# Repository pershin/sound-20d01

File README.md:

# Sound-20D01

## Sound-20D01MB

### Bill of Materials

| Reference                                                                      | Value                       | Package                      | Qnty |
|:------------------------------------------------------------------------------:| --------------------------- | ---------------------------- |:----:|
| C1, C2, C3, C4, C5, C10, C12, C13, C14, C16, C22, C25, C26, C28, C30, C42, C54 | 0.1uF, X7R, 50V             | 1206                         | 17   |
| C6, C7                                                                         | 15pF, C0G (NP0), 50V        | 1206                         | 2    |
| C8, C9                                                                         | 22pF, C0G (NP0), 50V        | 1206                         | 2    |
| C11, C41                                                                       | 1uF, X7R, 50V               | 1206                         | 2    |
| C15                                                                            | 4.7uF, X7R, 50V             | 1206                         | 1    |
| C18, C23                                                                       | 2.2nF, B32529C8222J000      | 2.5 x 6.5 x 7.3              | 2    |
| C19, C20, C33, C37, C40, C46, C47, C50, C51                                    | 2.2uF, X7R, 50V             | 1206                         | 9    |
| C21, C24, C45, C48, C49, C55, C17, C27                                         | 10uF, 16V                   | SMD 4 x 5.4                  | 8    |
| C29, C43                                                                       | 470uF, 63V, B41851F8477M000 | 12.5 x 20                    | 2    |
| C31                                                                            | 10uF, X7R, 50V              | 1210                         | 1    |
| C32, C39                                                                       | 4700uF, 35V                 | 18 x 35.5                    | 2    |
| C34, C38                                                                       | 0.68uF                      | 7.2 x 4.5 mm                 | 2    |
| C35, C36                                                                       | 0.22uF, X7R, 50V            | 1206                         | 2    |
| C44                                                                            | 47uF, 16V                   | SMD 6.3 x 5.4                | 1    |
| C52                                                                            | 47uF, 50V                   | SMD 6.3 x 7.7                | 1    |
| C53                                                                            | 0.33uF, X7R, 50V            | 1206                         | 1    |
| D1, D4, D5                                                                     | KP-3216MGC (Green)          | 1206                         | 3    |
| D2                                                                             | KP-3216SEC (Orange)         | 1206                         | 1    |
| D3                                                                             | CRS04                       | SOD-123F                     | 1    |
| F1                                                                             | MF-MSMF050-2                | 1812 (4532)                  | 1    |
| J1                                                                             | USBB-1J                     | USB-B1HSxx                   | 1    |
| J2                                                                             | X977B04                     | 7.62 mm                      | 1    |
| J3                                                                             | PLD-16                      | 2.54 mm                      | 1    |
| J4                                                                             | PLD-8                       | 2.54 mm                      | 1    |
| J5, J13                                                                        | PLS-6                       | 2.54 mm                      | 2    |
| J6, J7                                                                         | PLD-20                      | 2.54 mm                      | 2    |
| J8, J9                                                                         | JST XH B02B-XH-A            | 2.50 mm                      | 2    |
| J10                                                                            | JST VH B2P-VH               | 3.96 mm                      | 1    |
| J11, J14, JP1, JP2                                                             | PLS-3                       | 2.54 mm                      | 4    |
| J12                                                                            | PLS-4                       | 2.54 mm                      | 1    |
| L1, L2                                                                         | 22uH                        | Bourns SRR1260               | 2    |
| R1, R10, R17, R18, R22, R24                                                    | 10K, 1%                     | 1206                         | 6    |
| R2, R3, R15, R16                                                               | 4.7K, 1%                    | 1206                         | 4    |
| R4, R5, R8, R11, R12, R14                                                      | 22R, 1%                     | 1206                         | 6    |
| R6                                                                             | 390R, 1%                    | 1206                         | 1    |
| R7                                                                             | 51R, 1%                     | 1206                         | 1    |
| R9, R13                                                                        | 470R, 1%                    | 1206                         | 2    |
| R19, R20, R21, R23, R26                                                        | 1K, 1%                      | 1206                         | 5    |
| R25                                                                            | 680R, 1%                    | 1206                         | 1    |
| SW1                                                                            | DS1040-02RN                 | DIP SPSTx02                  | 1    |
| U1                                                                             | USBLC6-2SC6                 | SOT23-6L                     | 1    |
| U2                                                                             | STM32F446RCT6               | LQFP-64                      | 1    |
| U3                                                                             | PCM5142PW                   | TSSOP-28                     | 1    |
| U4                                                                             | TPA3123D2PWP                | HTSSOP-24 (PWP0024B)         | 1    |
| U5, U6                                                                         | FOD817B                     | DIP-4 7.62mm                 | 2    |
| U7, U8                                                                         | ADP3338AKCZ-3.3RL7          | SOT-223                      | 2    |
| U9                                                                             | L7805ABD2T-TR               | D2PAK (TO-263)               | 1    |
| X1                                                                             | SM7745HEV-12.288M           | 5 x 7 mm LCC Ceramic Package | 1    |
| Y1                                                                             | 32.768kHz (FC-135)          | SMD 3215                     | 1    |
| Y2                                                                             | 8MHz (AT-41CD2)             | SMD HC49-SM                  | 1    |

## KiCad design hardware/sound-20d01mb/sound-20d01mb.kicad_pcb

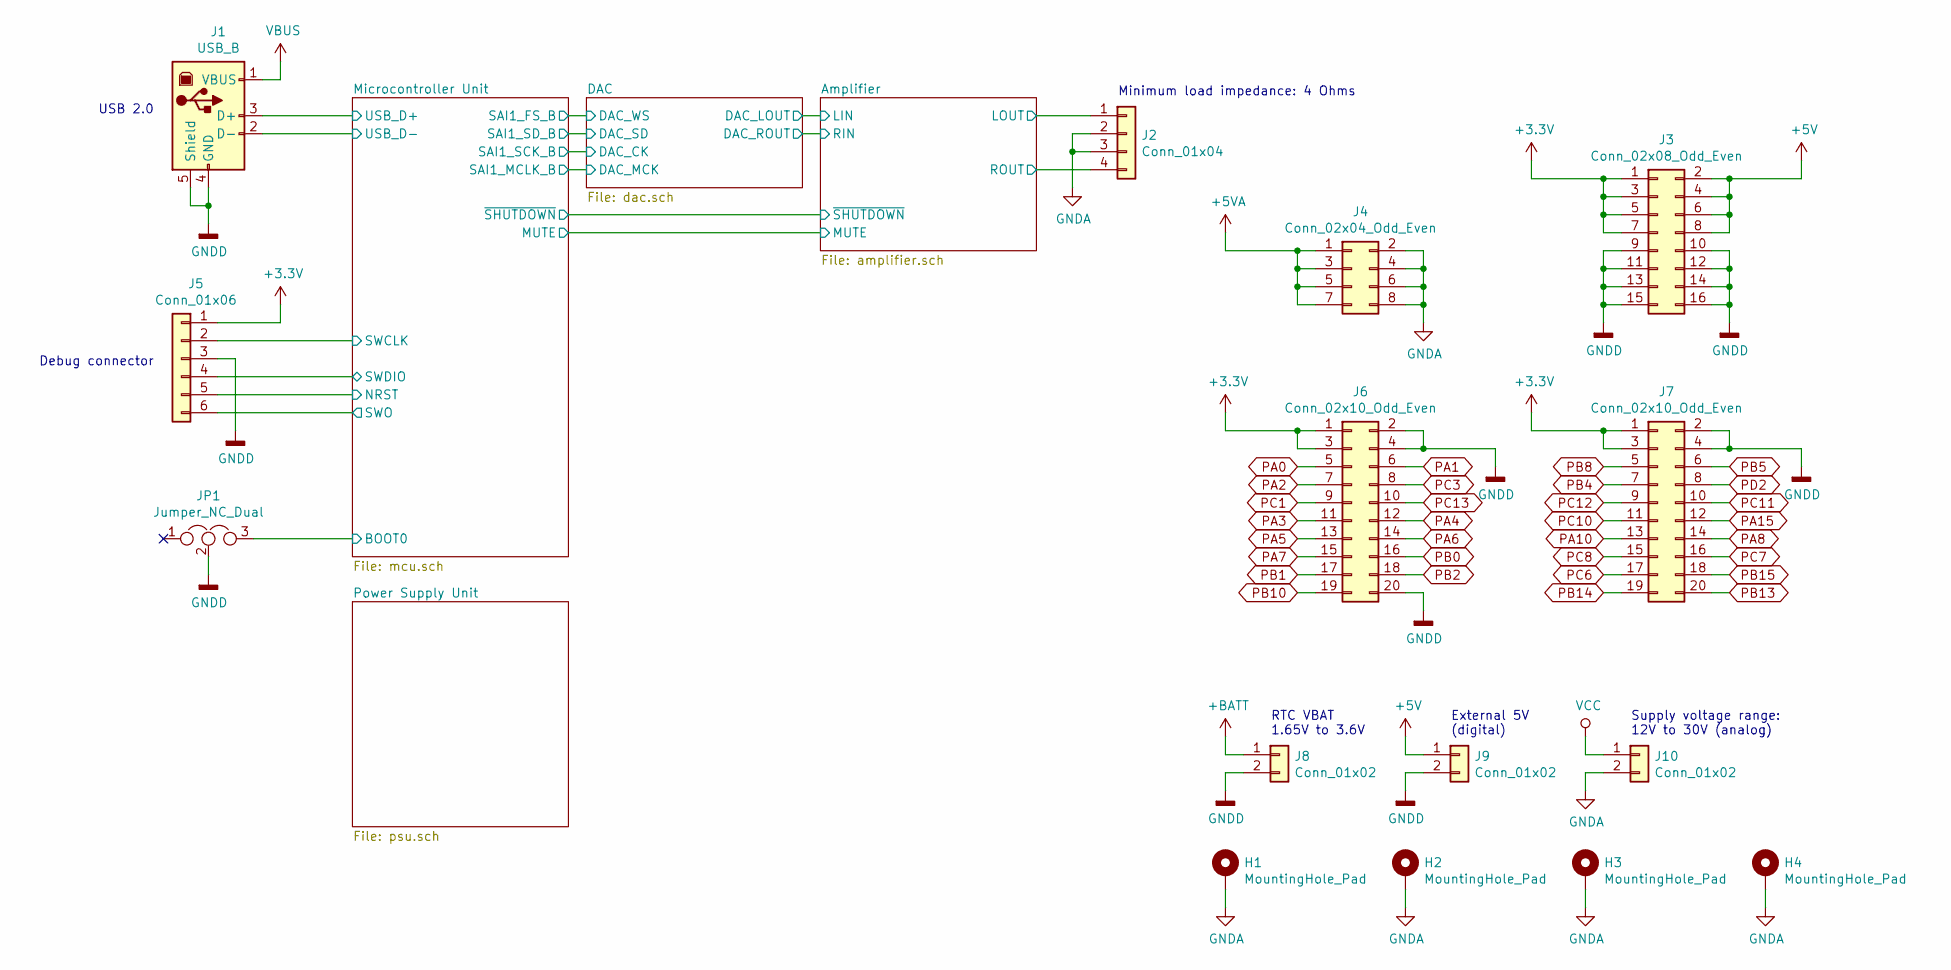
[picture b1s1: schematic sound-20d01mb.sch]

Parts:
H1, H2, H3, H4: MountingHole_Pad; MountingHole_3.2mm_M3_Pad_Via
J1: USB_B; USB_B_OST_USB-B1HSxx_Horizontal
J2: Conn_01x04; X977B04
J3: Conn_02x08_Odd_Even; PinHeader_2x08_P2.54mm_Vertical
J4: Conn_02x04_Odd_Even; PinHeader_2x04_P2.54mm_Vertical
J5: Conn_01x06; PinHeader_1x06_P2.54mm_Vertical
J6, J7: Conn_02x10_Odd_Even; PinHeader_2x10_P2.54mm_Vertical
J8, J9: Conn_01x02; JST_XH_B02B-XH-A_1x02_P2.50mm_Vertical
J10: Conn_01x02; JST_VH_B2P-VH_1x02_P3.96mm_Vertical
JP1: Jumper_NC_Dual; PinHeader_1x03_P2.54mm_Vertical

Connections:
+5V: J3.2, J3.4, J3.6, J3.8, J9.1; also elsewhere on the board
+5VA: J4.1, J4.3, J4.5, J4.7; also elsewhere on the board
+BATT: J8.1; also elsewhere on the board
/Amplifier/LOUT: J2.1; also elsewhere on the board
/Amplifier/ROUT: J2.4; also elsewhere on the board
/Microcontroller Unit/BOOT0: JP1.3; also elsewhere on the board
/Microcontroller Unit/NRST: J5.5; also elsewhere on the board
/Microcontroller Unit/SWCLK: J5.2; also elsewhere on the board
/Microcontroller Unit/SWDIO: J5.4; also elsewhere on the board
/Microcontroller Unit/SWO: J5.6; also elsewhere on the board
/Microcontroller Unit/USB_D+: J1.3 (D+); also elsewhere on the board
/Microcontroller Unit/USB_D-: J1.2 (D-); also elsewhere on the board
GNDA: H1.1, H2.1, H3.1, H4.1, J2.2, J2.3, J4.2, J4.4, J4.6, J4.8, J10.2; also elsewhere on the board
GNDD: J1.4 (GND), J1.5 (Shield), J3.9, J3.10, J3.11, J3.12, J3.13, J3.14, J3.15, J3.16, J5.3, J6.2, J6.4, J6.20, J7.2, J7.4, J8.2, J9.2, JP1.2; also elsewhere on the board
PA0: J6.5; also elsewhere on the board
PA1: J6.6; also elsewhere on the board
PA2: J6.7; also elsewhere on the board
PA3: J6.11; also elsewhere on the board
PA4: J6.12; also elsewhere on the board
PA5: J6.13; also elsewhere on the board
PA6: J6.14; also elsewhere on the board
PA7: J6.15; also elsewhere on the board
PA8: J7.14; also elsewhere on the board
PA10: J7.13; also elsewhere on the board
PA15: J7.12; also elsewhere on the board
PB0: J6.16; also elsewhere on the board
PB1: J6.17; also elsewhere on the board
PB2: J6.18; also elsewhere on the board
PB4: J7.7; also elsewhere on the board
PB5: J7.6; also elsewhere on the board
PB8: J7.5; also elsewhere on the board
PB10: J6.19; also elsewhere on the board
PB13: J7.20; also elsewhere on the board
PB14: J7.19; also elsewhere on the board
PB15: J7.18; also elsewhere on the board
PC1: J6.9; also elsewhere on the board
PC3: J6.8; also elsewhere on the board
PC6: J7.17; also elsewhere on the board
PC7: J7.16; also elsewhere on the board
PC8: J7.15; also elsewhere on the board
PC10: J7.11; also elsewhere on the board
PC11: J7.10; also elsewhere on the board
PC12: J7.9; also elsewhere on the board
PC13: J6.10; also elsewhere on the board
PD2: J7.8; also elsewhere on the board
VBUS: J1.1 (VBUS); also elsewhere on the board
VCC: J10.1; also elsewhere on the board

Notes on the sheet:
Minimum load impedance: 4 Ohms
Supply voltage range: 12V to 30V (analog)
Debug connector
USB 2.0
External 5V (digital)
RTC VBAT 1.65V to 3.6V

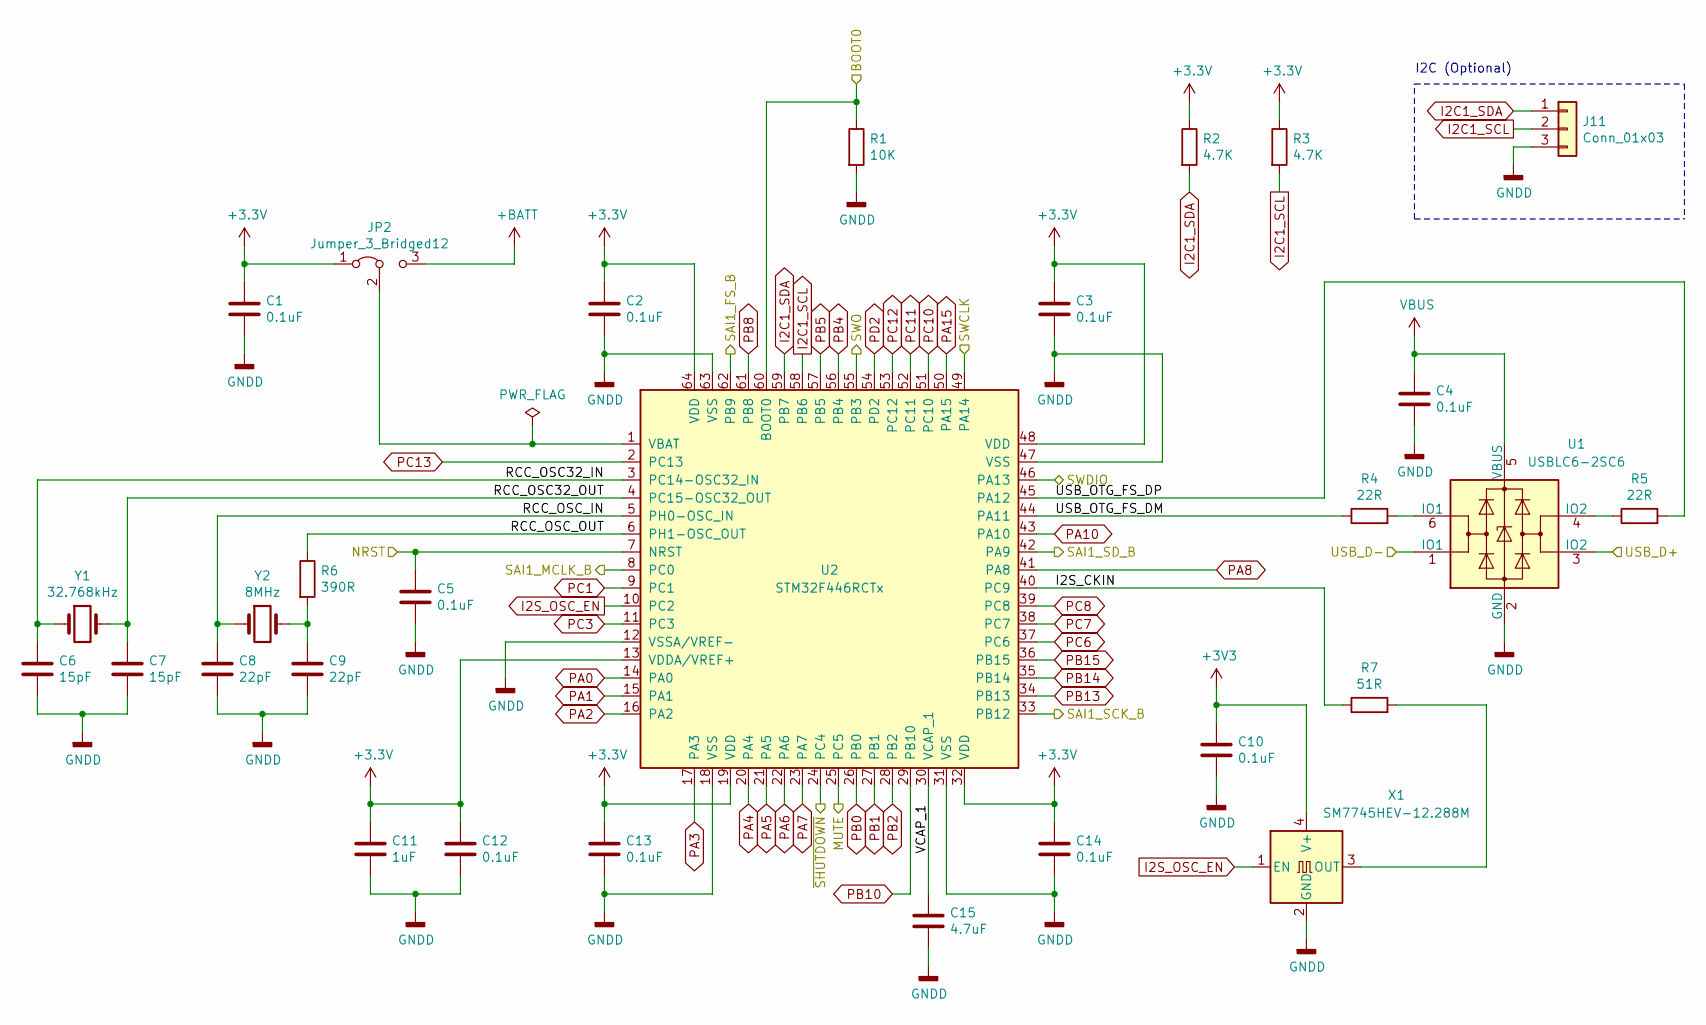
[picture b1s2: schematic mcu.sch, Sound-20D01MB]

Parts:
C1, C2, C3, C4, C5, C10, C12, C13, C14: 0.1uF; C_1206_3216Metric_Pad1.42x1.75mm_HandSolder
C6, C7: 15pF; C_1206_3216Metric_Pad1.42x1.75mm_HandSolder
C8, C9: 22pF; C_1206_3216Metric_Pad1.42x1.75mm_HandSolder
C11: 1uF; C_1206_3216Metric_Pad1.42x1.75mm_HandSolder
C15: 4.7uF; C_1206_3216Metric_Pad1.42x1.75mm_HandSolder
J11: Conn_01x03; PinHeader_1x03_P2.54mm_Vertical
JP2: Jumper_3_Bridged12; PinHeader_1x03_P2.54mm_Vertical
R1: 10K; R_1206_3216Metric_Pad1.42x1.75mm_HandSolder
R2, R3: 4.7K; R_1206_3216Metric_Pad1.42x1.75mm_HandSolder
R4, R5: 22R; R_1206_3216Metric_Pad1.42x1.75mm_HandSolder
R6: 390R; R_1206_3216Metric_Pad1.42x1.75mm_HandSolder
R7: 51R; R_1206_3216Metric_Pad1.42x1.75mm_HandSolder
U1: USBLC6-2SC6; SOT-23-6
U2: STM32F446RCTx; LQFP-64_10x10mm_P0.5mm
X1: SM7745HEV-12.288M; Oscillator_SMD_Fordahl_DFAS2-4Pin_7.3x5.1mm_HandSoldering
Y1: 32.768kHz; Crystal_SMD_3215-2Pin_3.2x1.5mm
Y2: 8MHz; Crystal_SMD_HC49-SD

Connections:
+BATT: JP2.3 (B); also elsewhere on the board
/Amplifier/MUTE: U2.25 (PC5); also elsewhere on the board
/Amplifier/~SHUTDOWN: U2.24 (PC4); also elsewhere on the board
/DAC/DAC_CK: U2.33 (PB12); also elsewhere on the board
/DAC/DAC_MCK: U2.8 (PC0); also elsewhere on the board
/DAC/DAC_SD: U2.42 (PA9); also elsewhere on the board
/DAC/DAC_WS: U2.62 (PB9); also elsewhere on the board
/Microcontroller Unit/BOOT0: R1.1, U2.60 (BOOT0); also elsewhere on the board
/Microcontroller Unit/I2S_CKIN: R7.1, U2.40 (PC9)
/Microcontroller Unit/NRST: C5.1, U2.7 (NRST); also elsewhere on the board
/Microcontroller Unit/RCC_OSC32_IN: C6.1, U2.3 (PC14-OSC32_IN), Y1.1
/Microcontroller Unit/RCC_OSC32_OUT: C7.1, U2.4 (PC15-OSC32_OUT), Y1.2
/Microcontroller Unit/RCC_OSC_IN: C8.1, U2.5 (PH0-OSC_IN), Y2.1
/Microcontroller Unit/RCC_OSC_OUT: R6.1, U2.6 (PH1-OSC_OUT)
/Microcontroller Unit/SWCLK: U2.49 (PA14); also elsewhere on the board
/Microcontroller Unit/SWDIO: U2.46 (PA13); also elsewhere on the board
/Microcontroller Unit/SWO: U2.55 (PB3); also elsewhere on the board
/Microcontroller Unit/USB_D+: U1.3 (IO2); also elsewhere on the board
/Microcontroller Unit/USB_D-: U1.1 (IO1); also elsewhere on the board
/Microcontroller Unit/USB_OTG_FS_DM: R4.1, U2.44 (PA11)
/Microcontroller Unit/USB_OTG_FS_DP: R5.2, U2.45 (PA12)
/Microcontroller Unit/VCAP_1: C15.1, U2.30 (VCAP_1)
GNDD: C1.2, C2.2, C3.2, C4.2, C5.2, C6.2, C7.2, C8.2, C9.2, C10.2, C11.2, C12.2, C13.2, C14.2, C15.2, J11.3, R1.2, U1.2 (GND), U2.12 (VSSA/VREF-), U2.18 (VSS), U2.31 (VSS), U2.47 (VSS), U2.63 (VSS), X1.2 (GND); also elsewhere on the board
I2C1_SCL: J11.2, R3.2, U2.58 (PB6); also elsewhere on the board
I2C1_SDA: J11.1, R2.2, U2.59 (PB7); also elsewhere on the board
I2S_OSC_EN: U2.10 (PC2), X1.1 (EN)
unnamed: C9.1, R6.2, Y2.2
unnamed: JP2.2 (C), U2.1 (VBAT)
unnamed: R4.2, U1.6 (IO1)
unnamed: R5.1, U1.4 (IO2)
unnamed: R7.2, X1.3 (OUT)
PA0: U2.14 (PA0); also elsewhere on the board
PA1: U2.15 (PA1); also elsewhere on the board
PA2: U2.16 (PA2); also elsewhere on the board
PA3: U2.17 (PA3); also elsewhere on the board
PA4: U2.20 (PA4); also elsewhere on the board
PA5: U2.21 (PA5); also elsewhere on the board
PA6: U2.22 (PA6); also elsewhere on the board
PA7: U2.23 (PA7); also elsewhere on the board
PA8: U2.41 (PA8); also elsewhere on the board
PA10: U2.43 (PA10); also elsewhere on the board
PA15: U2.50 (PA15); also elsewhere on the board
PB0: U2.26 (PB0); also elsewhere on the board
PB1: U2.27 (PB1); also elsewhere on the board
PB2: U2.28 (PB2); also elsewhere on the board
PB4: U2.56 (PB4); also elsewhere on the board
PB5: U2.57 (PB5); also elsewhere on the board
PB8: U2.61 (PB8); also elsewhere on the board
PB10: U2.29 (PB10); also elsewhere on the board
PB13: U2.34 (PB13); also elsewhere on the board
PB14: U2.35 (PB14); also elsewhere on the board
PB15: U2.36 (PB15); also elsewhere on the board
PC1: U2.9 (PC1); also elsewhere on the board
PC3: U2.11 (PC3); also elsewhere on the board
PC6: U2.37 (PC6); also elsewhere on the board
PC7: U2.38 (PC7); also elsewhere on the board
PC8: U2.39 (PC8); also elsewhere on the board
PC10: U2.51 (PC10); also elsewhere on the board
PC11: U2.52 (PC11); also elsewhere on the board
PC12: U2.53 (PC12); also elsewhere on the board
PC13: U2.2 (PC13); also elsewhere on the board
PD2: U2.54 (PD2); also elsewhere on the board
VBUS: C4.1, U1.5 (VBUS); also elsewhere on the board

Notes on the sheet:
I2C (Optional)

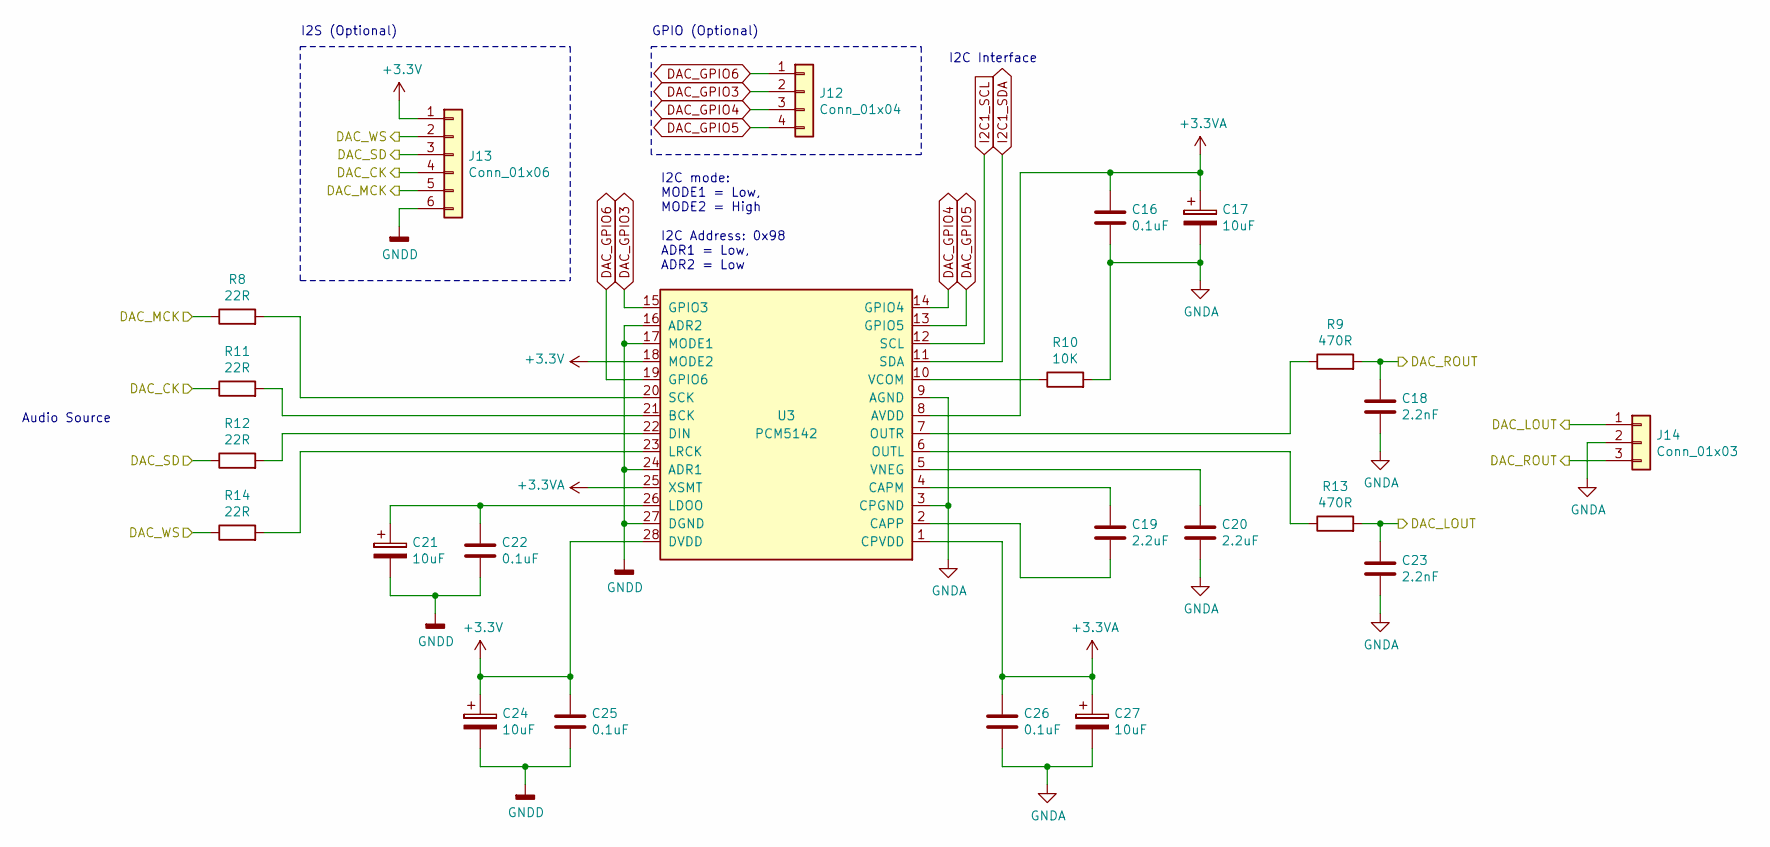
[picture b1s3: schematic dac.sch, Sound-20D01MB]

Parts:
C16, C22, C25, C26: 0.1uF; C_1206_3216Metric_Pad1.42x1.75mm_HandSolder
C17, C21, C24, C27: 10uF; CP_Elec_4x5.4
C18, C23: 2.2nF; C_Rect_L7.2mm_W2.5mm_P5.00mm_FKS2_FKP2_MKS2_MKP2
C19, C20: 2.2uF; C_1206_3216Metric_Pad1.42x1.75mm_HandSolder
J12: Conn_01x04; PinHeader_1x04_P2.54mm_Vertical
J13: Conn_01x06; PinHeader_1x06_P2.54mm_Vertical
J14: Conn_01x03; PinHeader_1x03_P2.54mm_Vertical
R8, R11, R12, R14: 22R; R_1206_3216Metric_Pad1.42x1.75mm_HandSolder
R9, R13: 470R; R_1206_3216Metric_Pad1.42x1.75mm_HandSolder
R10: 10K; R_1206_3216Metric_Pad1.42x1.75mm_HandSolder
U3: PCM5142; TSSOP-28_4.4x9.7mm_P0.65mm

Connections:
+3.3VA: C16.1, C17.1, C26.1, C27.1, U3.1 (CPVDD), U3.8 (AVDD), U3.25 (XSMT); also elsewhere on the board
/DAC/DAC_CK: J13.4, R11.1; also elsewhere on the board
/DAC/DAC_LOUT: C23.1, J14.1, R13.2; also elsewhere on the board
/DAC/DAC_MCK: J13.5, R8.1; also elsewhere on the board
/DAC/DAC_ROUT: C18.1, J14.3, R9.2; also elsewhere on the board
/DAC/DAC_SD: J13.3, R12.1; also elsewhere on the board
/DAC/DAC_WS: J13.2, R14.1; also elsewhere on the board
DAC_GPIO3: J12.2, U3.15 (GPIO3)
DAC_GPIO4: J12.3, U3.14 (GPIO4)
DAC_GPIO5: J12.4, U3.13 (GPIO5)
DAC_GPIO6: J12.1, U3.19 (GPIO6)
GNDA: C16.2, C17.2, C18.2, C20.2, C23.2, C26.2, C27.2, J14.2, R10.2, U3.3 (CPGND), U3.9 (AGND); also elsewhere on the board
GNDD: C21.2, C22.2, C24.2, C25.2, J13.6, U3.16 (ADR2), U3.17 (MODE1), U3.24 (ADR1), U3.27 (DGND); also elsewhere on the board
I2C1_SCL: U3.12 (SCL); also elsewhere on the board
I2C1_SDA: U3.11 (SDA); also elsewhere on the board
unnamed: C19.1, U3.4 (CAPM)
unnamed: C19.2, U3.2 (CAPP)
unnamed: C20.1, U3.5 (VNEG)
unnamed: C21.1, C22.1, U3.26 (LDOO)
unnamed: R8.2, U3.20 (SCK)
unnamed: R9.1, U3.7 (OUTR)
unnamed: R10.1, U3.10 (VCOM)
unnamed: R11.2, U3.21 (BCK)
unnamed: R12.2, U3.22 (DIN)
unnamed: R13.1, U3.6 (OUTL)
unnamed: R14.2, U3.23 (LRCK)

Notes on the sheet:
Audio Source
I2C Interface
I2C mode: MODE1 = Low, MODE2 = High I2C Address: 0x98 ADR1 = Low, ADR2 = Low
GPIO (Optional)
I2S (Optional)

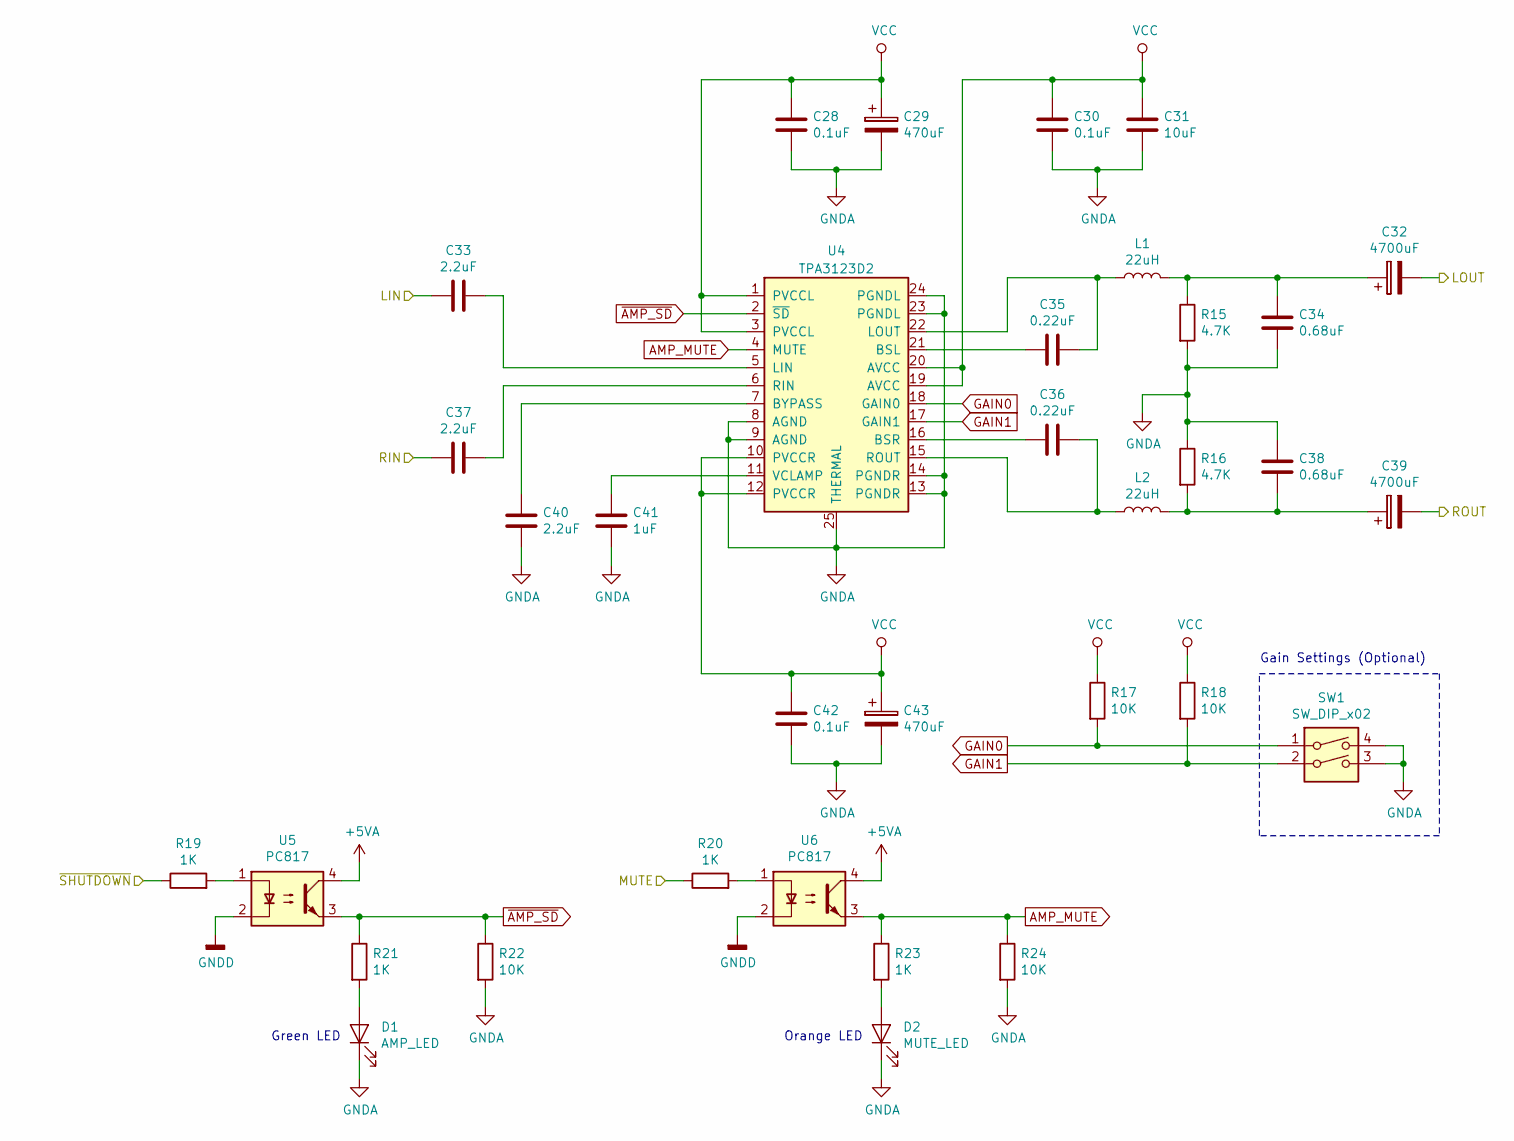
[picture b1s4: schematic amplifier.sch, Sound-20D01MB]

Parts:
C28, C30, C42: 0.1uF; C_1206_3216Metric_Pad1.42x1.75mm_HandSolder
C29, C43: 470uF; CP_Radial_D12.5mm_P5.00mm
C31: 10uF; C_1210_3225Metric_Pad1.42x2.65mm_HandSolder
C32, C39: 4700uF; CP_Radial_D18.0mm_P7.50mm
C33, C37, C40: 2.2uF; C_1206_3216Metric_Pad1.42x1.75mm_HandSolder
C34, C38: 0.68uF; C_Rect_L7.2mm_W4.5mm_P5.00mm_FKS2_FKP2_MKS2_MKP2
C35, C36: 0.22uF; C_1206_3216Metric_Pad1.42x1.75mm_HandSolder
C41: 1uF; C_1206_3216Metric_Pad1.42x1.75mm_HandSolder
D1: AMP_LED; LED_1206_3216Metric_Pad1.42x1.75mm_HandSolder
D2: MUTE_LED; LED_1206_3216Metric_Pad1.42x1.75mm_HandSolder
L1, L2: 22uH; L_Bourns_SRR1260
R15, R16: 4.7K; R_1206_3216Metric_Pad1.42x1.75mm_HandSolder
R17, R18, R22, R24: 10K; R_1206_3216Metric_Pad1.42x1.75mm_HandSolder
R19, R20, R21, R23: 1K; R_1206_3216Metric_Pad1.42x1.75mm_HandSolder
SW1: SW_DIP_x02; SW_DIP_SPSTx02_Slide_9.78x7.26mm_W7.62mm_P2.54mm
U4: TPA3123D2; PWP0024B
U5, U6: PC817; DIP-4_W7.62mm

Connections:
+5VA: U5.4, U6.4; also elsewhere on the board
/Amplifier/LOUT: C32.2; also elsewhere on the board
/Amplifier/MUTE: R20.1; also elsewhere on the board
/Amplifier/ROUT: C39.2; also elsewhere on the board
/Amplifier/~SHUTDOWN: R19.1; also elsewhere on the board
/DAC/DAC_LOUT: C33.1; also elsewhere on the board
/DAC/DAC_ROUT: C37.1; also elsewhere on the board
AMP_MUTE: R23.1, R24.1, U4.4 (MUTE), U6.3
GAIN0: R17.2, SW1.1, U4.18 (GAIN0)
GAIN1: R18.2, SW1.2, U4.17 (GAIN1)
GNDA: C28.2, C29.2, C30.2, C31.2, C34.2, C38.1, C40.2, C41.2, C42.2, C43.2, D1.1 (K), D2.1 (K), R15.2, R16.1, R22.2, R24.2, SW1.3, SW1.4, U4.8 (AGND), U4.9 (AGND), U4.13 (PGNDR), U4.14 (PGNDR), U4.23 (PGNDL), U4.24 (PGNDL), U4.25 (THERMAL); also elsewhere on the board
GNDD: U5.2, U6.2; also elsewhere on the board
unnamed: C32.1, C34.1, L1.2, R15.1
unnamed: C33.2, U4.5 (LIN)
unnamed: C35.1, U4.21 (BSL)
unnamed: C35.2, L1.1, U4.22 (LOUT)
unnamed: C36.1, U4.16 (BSR)
unnamed: C36.2, L2.1, U4.15 (ROUT)
unnamed: C37.2, U4.6 (RIN)
unnamed: C38.2, C39.1, L2.2, R16.2
unnamed: C40.1, U4.7 (BYPASS)
unnamed: C41.1, U4.11 (VCLAMP)
unnamed: D1.2 (A), R21.2
unnamed: D2.2 (A), R23.2
unnamed: R19.2, U5.1
unnamed: R20.2, U6.1
VCC: C28.1, C29.1, C30.1, C31.1, C42.1, C43.1, R17.1, R18.1, U4.1 (PVCCL), U4.3 (PVCCL), U4.10 (PVCCR), U4.12 (PVCCR), U4.19 (AVCC), U4.20 (AVCC); also elsewhere on the board
~AMP_SD: R21.1, R22.1, U4.2 (~SD), U5.3

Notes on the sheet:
Gain Settings (Optional)
Orange LED
Green LED

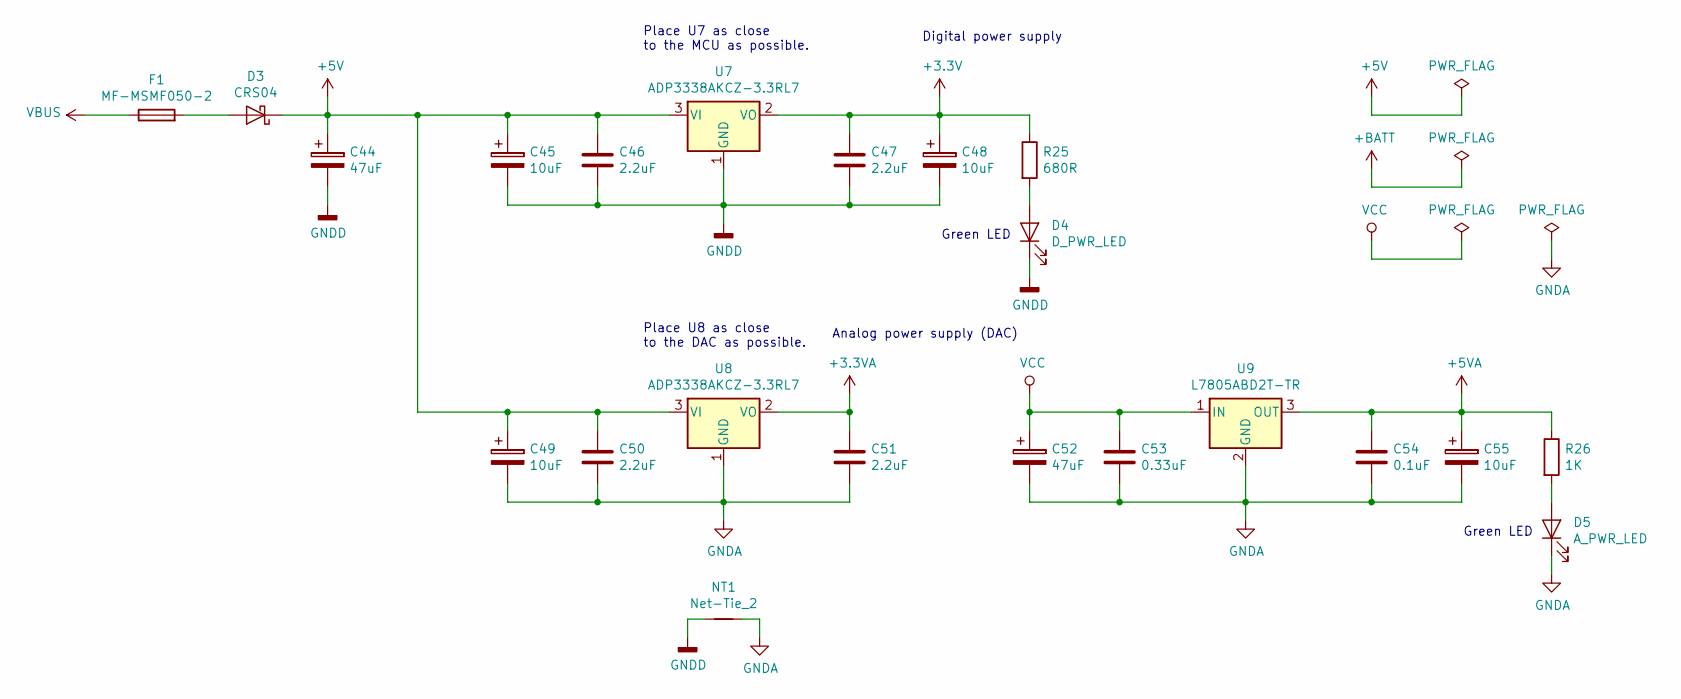
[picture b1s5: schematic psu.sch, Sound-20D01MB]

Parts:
C44: 47uF; CP_Elec_6.3x5.4
C45, C48, C49, C55: 10uF; CP_Elec_4x5.4
C46, C47, C50, C51: 2.2uF; C_1206_3216Metric_Pad1.42x1.75mm_HandSolder
C52: 47uF; CP_Elec_6.3x7.7
C53: 0.33uF; C_1206_3216Metric_Pad1.42x1.75mm_HandSolder
C54: 0.1uF; C_1206_3216Metric_Pad1.42x1.75mm_HandSolder
D3: CRS04; D_SOD-123F
D4: D_PWR_LED; LED_1206_3216Metric_Pad1.42x1.75mm_HandSolder
D5: A_PWR_LED; LED_1206_3216Metric_Pad1.42x1.75mm_HandSolder
F1: MF-MSMF050-2; Fuse_1812_4532Metric_Pad1.30x3.40mm_HandSolder
NT1: Net-Tie_2; NetTie-2_SMD_Pad2.0mm
R25: 680R; R_1206_3216Metric_Pad1.42x1.75mm_HandSolder
R26: 1K; R_1206_3216Metric_Pad1.42x1.75mm_HandSolder
U7, U8: ADP3338AKCZ-3.3RL7; SOT-223-3_TabPin2
U9: L7805ABD2T-TR; TO-263-2

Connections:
+3.3VA: C51.1, U8.2 (VO); also elsewhere on the board
+5V: C44.1, C45.1, C46.1, C49.1, C50.1, D3.1 (K), U7.3 (VI), U8.3 (VI); also elsewhere on the board
+5VA: C54.1, C55.1, R26.1, U9.3 (OUT); also elsewhere on the board
GNDA: C49.2, C50.2, C51.2, C52.2, C53.2, C54.2, C55.2, D5.1 (K), NT1.2, U8.1 (GND), U9.2 (GND); also elsewhere on the board
GNDD: C44.2, C45.2, C46.2, C47.2, C48.2, D4.1 (K), NT1.1, U7.1 (GND); also elsewhere on the board
unnamed: D3.2 (A), F1.2
unnamed: D4.2 (A), R25.2
unnamed: D5.2 (A), R26.2
VBUS: F1.1; also elsewhere on the board
VCC: C52.1, C53.1, U9.1 (IN); also elsewhere on the board

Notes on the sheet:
Analog power supply (DAC)
Digital power supply
Place U7 as close to the MCU as possible.
Place U8 as close to the DAC as possible.
Green LED

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
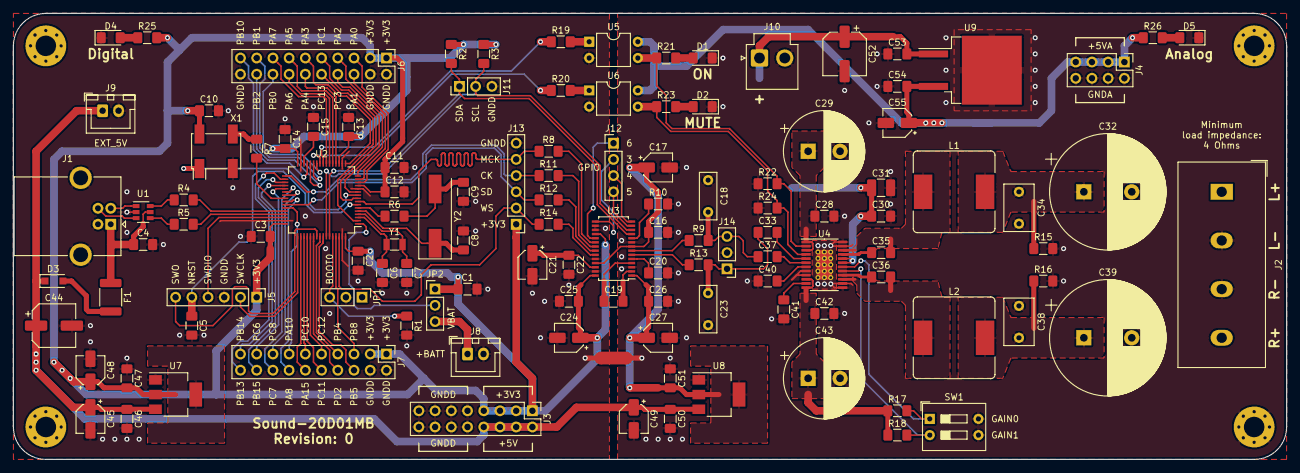
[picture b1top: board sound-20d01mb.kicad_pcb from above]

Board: 2 copper layers, 199.4 x 69.8 mm, 123 parts (0 on the bottom side), 109 nets.

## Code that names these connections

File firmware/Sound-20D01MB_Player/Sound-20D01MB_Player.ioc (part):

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PH0-OSC_IN.Signal=RCC_OSC_IN
Mcu.UserName=STM32F446RCTx
PB10.Mode=Simplex_Bidirectional_Master
PA3.GPIOParameters=GPIO_Label
PA6.GPIO_Label=VOL_U
PD2.GPIOParameters=GPIO_PuPd
PA2.GPIOParameters=GPIO_Label
RCC.SYSCLKSource=RCC_SYSCLKSOURCE_PLLCLK
PC11.GPIO_PuPd=GPIO_PULLUP
PB1.GPIO_PuPd=GPIO_PULLUP
PB6.Signal=I2C1_SCL
PB6.Mode=I2C
PH0-OSC_IN.Mode=HSE-External-Oscillator
PA0-WKUP.GPIOParameters=GPIO_Label
RCC.HSE_VALUE=8000000
PB2.Signal=SDIO_CK
PB0.GPIOParameters=GPIO_PuPd
PA1.GPIOParameters=GPIO_Label
PC14-OSC32_IN.Mode=LSE-External-Oscillator
PC4.GPIO_Label=SHUTDOWN
PC9.Mode=Audio_ClockIn
PB7.Signal=I2C1_SDA
PH1-OSC_OUT.Mode=HSE-External-Oscillator
PC8.GPIOParameters=GPIO_PuPd
Mcu.Package=LQFP64
PB9.Signal=SAI1_FS_B
PB1.Signal=SDIO_D2
PA6.Signal=GPXTI6
PB12.Mode=SAI_B_MasterWithClock
PA2.GPIO_Label=PREV
PA5.GPIOParameters=GPIO_Label
PC11.Mode=SD_4_bits_Wide_bus
PC5.Signal=GPIO_Output
PC2.GPIO_Label=I2S_OSC_EN
PC4.GPIOParameters=GPIO_Label
PA3.Signal=GPXTI3
PA6.GPIOParameters=GPIO_Label
PC15-OSC32_OUT.Mode=LSE-External-Oscillator
PB8.GPIOParameters=GPIO_Label
PD2.GPIO_PuPd=GPIO_PULLUP
PC11.Signal=SDIO_D3
PC8.Signal=SDIO_D0
PC4.Signal=GPIO_Output
PC2.Signal=GPIO_Output
PC0.Signal=SAI1_MCLK_B
PC14-OSC32_IN.Signal=RCC_OSC32_IN
PC11.GPIOParameters=GPIO_PuPd
PA0-WKUP.GPIO_Label=DISP_LATCH
PA0-WKUP.Signal=GPIO_Output
PC0.Mode=SAI_B_MasterWithClock
PA13.Signal=SYS_JTMS-SWDIO
PB8.GPIO_Label=SD_DETECT
PA9.Mode=SAI_B_MasterWithClock
PB9.Mode=SAI_B_MasterWithClock
PC5.GPIOParameters=GPIO_Label
PA9.Signal=SAI1_SD_B
PC15-OSC32_OUT.Signal=RCC_OSC32_OUT
PA1.Signal=GPIO_Output
PB10.Signal=SPI2_SCK
PD2.Mode=SD_4_bits_Wide_bus
PA5.Signal=GPXTI5
PB0.Mode=SD_4_bits_Wide_bus
board=custom
PC2.GPIOParameters=GPIO_Label
PA1.GPIO_Label=DISP_EN
PH1-OSC_OUT.Signal=RCC_OSC_OUT
Mcu.Name=STM32F446R(C-E)Tx
PA2.Signal=GPXTI2
PC8.Mode=SD_4_bits_Wide_bus
PC8.GPIO_PuPd=GPIO_PULLUP
PB3.Signal=SYS_JTDO-SWO
RCC.SYSCLKFreq_VALUE=180000000
PA5.GPIO_Label=VOL_D
PC5.GPIO_Label=MUTE
PB2.Mode=SD_4_bits_Wide_bus
PB7.Mode=I2C
PA14.Signal=SYS_JTCK-SWCLK
PB1.Mode=SD_4_bits_Wide_bus
PB8.Signal=GPIO_Input
PC9.Signal=I2S_CKIN
PD2.Signal=SDIO_CMD
PB0.Signal=SDIO_D1
PC1.Signal=SPI2_MOSI
PB12.Signal=SAI1_SCK_B
PB0.GPIO_PuPd=GPIO_PULLUP
PC1.Mode=Simplex_Bidirectional_Master
PA3.GPIO_Label=NEXT
PB1.GPIOParameters=GPIO_PuPd

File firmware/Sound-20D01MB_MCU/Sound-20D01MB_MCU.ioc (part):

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PH0-OSC_IN.Signal=RCC_OSC_IN
Mcu.UserName=STM32F446RCTx
PA11.Mode=Device_Only
RCC.SYSCLKSource=RCC_SYSCLKSOURCE_PLLCLK
PA12.Signal=USB_OTG_FS_DP
PB6.Signal=I2C1_SCL
PB6.Mode=I2C
PH0-OSC_IN.Mode=HSE-External-Oscillator
RCC.HSE_VALUE=8000000
PC14-OSC32_IN.Mode=LSE-External-Oscillator
PC4.GPIO_Label=SHUTDOWN
PC9.Mode=Audio_ClockIn
PB7.Signal=I2C1_SDA
PH1-OSC_OUT.Mode=HSE-External-Oscillator
PB9.Signal=SAI1_FS_B
Mcu.Package=LQFP64
PB12.Mode=SAI_B_MasterWithClock
PC5.Signal=GPIO_Output
PA4.GPIO_Label=DISPLAY_LATCH
PC2.GPIO_Label=I2S_OSC_EN
PC4.GPIOParameters=GPIO_Label
PA5.Mode=Simplex_Bidirectional_Master
PC15-OSC32_OUT.Mode=LSE-External-Oscillator
PA7.Mode=Simplex_Bidirectional_Master
PC4.Signal=GPIO_Output
PC2.Signal=GPIO_Output
PC0.Signal=SAI1_MCLK_B
PC14-OSC32_IN.Signal=RCC_OSC32_IN
PC0.Mode=SAI_B_MasterWithClock
PA13.Signal=SYS_JTMS-SWDIO
PA9.Mode=SAI_B_MasterWithClock
PB9.Mode=SAI_B_MasterWithClock
PC5.GPIOParameters=GPIO_Label
PA9.Signal=SAI1_SD_B
PC15-OSC32_OUT.Signal=RCC_OSC32_OUT
PA5.Signal=SPI1_SCK
board=custom
PC2.GPIOParameters=GPIO_Label
PH1-OSC_OUT.Signal=RCC_OSC_OUT
PA4.GPIOParameters=GPIO_Label
Mcu.Name=STM32F446R(C-E)Tx
PB3.Signal=SYS_JTDO-SWO
PA4.Signal=GPIO_Output
RCC.SYSCLKFreq_VALUE=180000000
PA12.Mode=Device_Only
PC5.GPIO_Label=MUTE
PB7.Mode=I2C
PA11.Signal=USB_OTG_FS_DM
PA14.Signal=SYS_JTCK-SWCLK
PC9.Signal=I2S_CKIN
PB12.Signal=SAI1_SCK_B
PA7.Signal=SPI1_MOSI

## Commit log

2021-07-01 Added new sheets (mcu.sch, dac.sch and amplifier.sch)
2021-07-01 Added TPA3122D2
2021-07-01 Updated amplifier schematic
2021-07-02 Added PGA2311P
2021-07-02 Added PCM5102A
2021-07-02 Fixed -+VA
2021-07-02 Added power supply unit
2021-07-02 Updated power supply unit
2021-07-02 Added STM32F446RCTx
2021-07-04 Updated MCU schematic
2021-07-04 Updated DAC
2021-07-04 Added Gain Settings
2021-07-04 Connected MCU to DAC
2021-07-04 Added Debug connector
2021-07-04 Updated sound-20d01mb.sch
2021-07-05 Added SWO
2021-07-05 Added OSC32
2021-07-05 Fixed mounting hole
2021-07-06 Added ADG3304BRUZ
2021-07-08 Updated amplifier.sch
2021-07-09 Updated PSU
2021-07-09 Updated text
2021-07-10 Added LM27762
2021-07-12 THT to SMD Capacitor
2021-07-12 THT to SMD Capacitor (2)
2021-07-15 Added PC817
2021-08-29 Added oscillators sheet
2021-08-29 Added AD1938
2021-08-31 Created firmware project
2021-09-11 Updated schematics
2021-09-12 Added USB audio
2021-09-12 Added SPI for Audio codec
2021-09-12 Project clean
2021-09-12 Updated .gitignore
2021-09-12 Added OSC
2021-09-12 Added PCM5142
2021-09-16 Added I2C Volume control
2021-09-18 New amplifier (TPA3123D2)
2021-09-18 Updated PSU and DAC
2021-09-19 Added X977B04
2021-09-20 Added DAC GPIO
2021-09-21 Updated schematic
2021-09-25 Added fuse for USB
2021-09-25 Connected GNDD and GNDA
2021-09-25 Updated mounting holes
2021-09-25 Added USBLC6-2 Datasheet
2021-09-26 Updated fuse footprint
2021-09-26 Added GPIO for MCU
2021-11-17 Added RTC-BAT
2021-11-19 Load capacitance for RTC Crystal
2021-11-19 Updated dac.sch
2021-11-21 Added SD and MUTE to schematic
2021-11-21 Added L7805
2021-11-21 Added connector for +5VA
2021-11-22 Added connector for I2C
2021-11-22 Added MUTE and SD to firmware
2021-11-22 Removed oscillators.sch
2021-11-22 Added datasheet for sm77h
2021-11-22 Removed SPI driver
2021-11-22 Fixed TPA3123D2
2021-11-22 Fixed VCAP_1
2021-11-23 PCM5142 I2C Mode
2021-11-23 Annotate schematic
2021-11-23 Updated: annotate schematic
2021-11-25 Updated footprints
2021-11-25 Updated PCB
2021-11-25 New volume
2021-11-25 Updated C52 footprint
2021-11-29 Added PWP0024B
2021-11-30 Updated PWP0024B
2021-11-30 Added text EXT_5V
2021-12-01 All connections are connected
2021-12-02 New Gerber files
2021-12-04 Added debug for BSP_AUDIO_Init
2021-12-04 Added USB-Audio PDF
2021-12-05 Added volume control to firmware
2021-12-05 Removed hack for EP0_RxReady
2021-12-05 Removed hacks
2021-12-06 Added Bill of Materials
2021-12-09 Added init for PCM5142
2021-12-16 Updated R25
2021-12-25 Added report (PDF)
2022-01-22 Added RTC Driver
2023-06-10 Added SD player
2023-06-13 Save state
2023-09-18 Updated player
2023-09-18 SPI to SDIO
2023-09-21 Added DMA SDIO
2023-09-22 Removed FAT and USB
2023-09-23 Added clusters
2023-09-27 Added display (SPI)
2023-11-01 Added codec
2023-11-02 Fixed file size
2023-11-02 Added PLAC header
2023-11-02 Added PLAC to player (software)
2023-11-02 New function is_int8_buffer
2023-11-02 Added empy flag and fixed is_int8_buffer
2023-11-04 Added Predictor from ALAC
2023-11-04 Removed ALAC code
2023-11-05 Removed plac_read_8
2023-11-05 Fix empty
2023-11-10 Real SD device for FS
2023-11-12 Fixed large SD
2024-11-11 Added playlist
2026-03-26 Add delta encoding
2026-03-26 Add --pcm
2026-03-26 Add size diff script
2026-03-26 Add Cleanup label
2026-03-26 Fix author
2026-03-26 Updated utils
2026-03-26 Fix H
2026-03-26 Updated API
2026-03-26 Updated signal_handler
2026-03-27 Add PLAC Codec Specification
2026-03-27 Add format.sh
2026-03-27 Fix format.sh
2026-03-27 Add .clang-format
